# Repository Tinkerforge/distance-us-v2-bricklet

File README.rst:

Distance US Bricklet 2.0
========================

This repository contains the firmware source code and the hardware design
files. The documentation generator configs can be found at
https://github.com/Tinkerforge/generators

Repository Content
------------------

software/:
 * examples/: Examples for all supported languages
 * build/: Compiled files
 * src/: Source code of firmware
 * Makefile: Makefile to build project

hardware/:
 * Contains KiCad project files and additionally schematics as PDF

datasheets/:
 * Contains datasheets for sensors and complex ICs that are used

Hardware
--------

The hardware is designed with the open source EDA Suite KiCad
(http://www.kicad.org). Before you are able to open the files,
you have to install the Tinkerforge kicad-libraries
(https://github.com/Tinkerforge/kicad-libraries). You can either clone
them directly in hardware/ or clone them in a separate folder and
symlink them into hardware/
(ln -s kicad_path/kicad-libraries project_path/hardware). After that you
can open the .pro file in hardware/ with KiCad and from there view and
modify the schematics and the PCB layout.

Software
--------

If you want to do your own Brick/Bricklet firmware development we highly
recommend that you use our build environment setup script and read the
tutorial (https://www.tinkerforge.com/en/doc/Tutorials/Tutorial_Build_Environment/Tutorial.html).

To compile the C code we recommend you to install the newest GNU Arm Embedded
Toolchain (https://launchpad.net/gcc-arm-embedded/+download).
You also need to install bricklib2 (https://github.com/Tinkerforge/bricklib2).

You can either clone it directly in software/src/ or clone it in a
separate folder and symlink it into software/src/
(ln -s bricklib_path/bricklib2 project_path/software/src/). Finally make sure to
have CMake installed (http://www.cmake.org/cmake/resources/software.html).

After that you can build the firmware by invoking make in software/.
The firmware (.zbin) can then be found in software/build/ and uploaded
with brickv (click button "Flashing" on start screen).

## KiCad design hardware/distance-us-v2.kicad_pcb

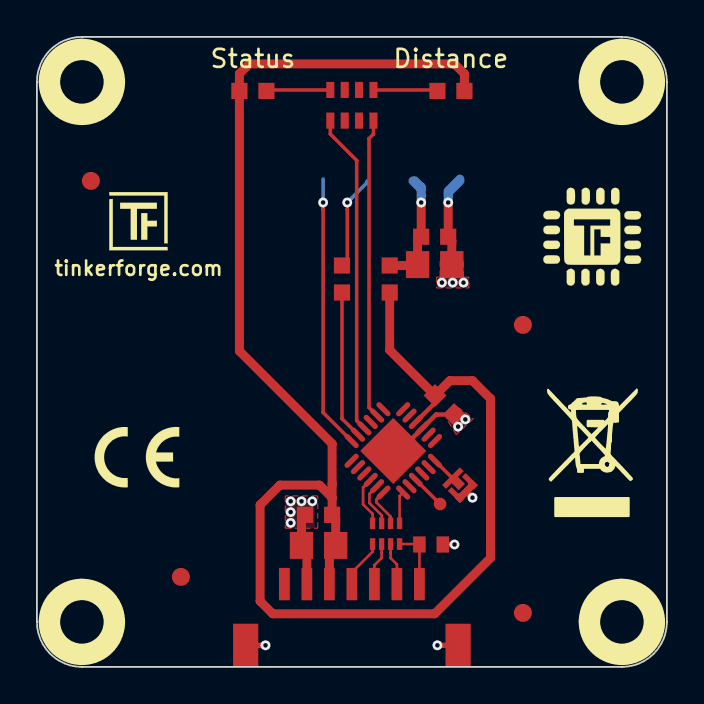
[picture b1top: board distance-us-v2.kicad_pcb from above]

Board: 2 copper layers, 35.0 x 35.0 mm, 27 parts (1 on the bottom side), 20 nets.

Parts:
C1: 220pF; C0402E
C2, C6: 10uF; C0805E
C3, C7: 1uF; C0603F
C4: 100nF; C0603F
D1: BLUE; D0603F
D2: GREEN; D0603F
Fiducial_Mark: VAL**; Fiducial_Mark
Fiducial_Mark#2, Fiducial_Mark#3, Fiducial_Mark#4: VAL**; Fiducial_Mark
L1: FB; R0603F
P1: CON-SENSOR2
P2: DEBUG; DEBUG_PAD
P3: BOOT; SolderJumper
R1: 1k; R0603F
RP1: 82; 4X0402
RP2: 1k; 4X0603
U1: XMC1100; QFN24-4x4mm-0.5mm
U2, U3, U4, U5: DRILL; DRILL_NP
U6: HRLV-EZ; HRLV-EZ(SMD_EX)
VAL: CE_5mm
VAL#2: WEEE_7mm

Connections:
3V3: C2.1, C3.1, C4.1, D1.1, D2.1, L1.1, P1.3, U1.10
GND: C1.2, C2.2, C3.2, C4.2, C6.2, C7.2, P1.2, P1.EP, P3.1, U1.9, U1.EXP, U6.7
unnamed: C1.1, P1.7, RP1.4
unnamed: C6.1, C7.1, L1.2, U6.6
unnamed: D1.2, RP2.1
unnamed: D2.2, RP2.4
unnamed: P1.4, RP1.1
unnamed: P1.5, RP1.2
unnamed: P1.6, RP1.3
unnamed: P2.1, U1.3
unnamed: P3.2, U1.6
unnamed: R1.1, U6.5
unnamed: RP2.5, U1.14
unnamed: RP2.8, U1.16
Ranging: U1.18, U6.4
S-CLK: RP1.7, U1.23
S-CS: RP1.8, U1.22
S-MISO: RP1.5, U1.1
S-MOSI: RP1.6, U1.24
Serial: R1.2, U1.17

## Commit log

2018-09-26 initial push
2018-09-26 Add correct readme flavor
2018-09-26 Add .gitignore
2018-09-26 create schematic
2018-09-26 added datasheet HRLV-EZ
2018-09-26 fix comment, fix footprints
2018-09-26 created pcb design
2018-09-26 changed schematic
2018-09-26 added 3d file to footprint HRLV-EZ
2019-03-15 Add sym-lib-table
2019-03-19 changed sensor footprint, new pcb design
2019-03-19 Add simple API for Bricklet and UART driver for MaxBotix sensor
2019-03-20 drc check, plotted 2 differnt footprints of HRLV for prototyp
2019-04-08 new 35x35 design
2019-04-17 changed HRLV footprint and centered it
2019-04-23 Add 2/10Hz support
2019-04-26 Implement API for distance LED and update rate configuration
2019-05-02 Remove TODO
2019-05-03 Add auto-generated examples
2019-05-07 add fiducials, drc
2019-05-13 fix file names
2019-05-14 Update rust examples.
2019-08-14 Turn logging off
2019-08-14 Add changelog entry for inital version
2019-08-15 add 3d data
2019-08-15 add schematic
2019-08-22 c: Adapt to bindings changes
2019-08-22 Remove development
2020-01-13 examples: Use python3 input instead of python2 raw_input.
2020-01-13 examples: mqtt: Remove trailing whitespace.
2020-08-19 Add uc examples.
2020-08-25 uc: Fix whitespace
2020-08-27 uc: Fix warnings.
2020-09-02 uc: Add example driver note.
2020-10-16 uc: Fix divisor type.
2021-10-25 Update KiCad link
    https://www.kicad.org/blog/2021/10/Avoid-links-to-former-kicad-domain/
2022-04-19 examples: uc: Rename TF_HalContext to TF_HAL.
2022-04-27 uc: Adapt to bindings changes
2022-07-06 Add license files.
2025-10-04 Fix compatibility with new Docker build image (GCC 14.2.1)
